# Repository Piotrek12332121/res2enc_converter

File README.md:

# res2enc_converter
It's a low-cost resolver2encoder converter to convert signals in motors found in old industrial robots

It uses AD2S1210 chip to generate excitation signals for resolver, measure analog signals, convert them and generate encoder-like signals that can be used with modern servo drives. Board can be powered by 24 or 12 V and has opto-isolated output.

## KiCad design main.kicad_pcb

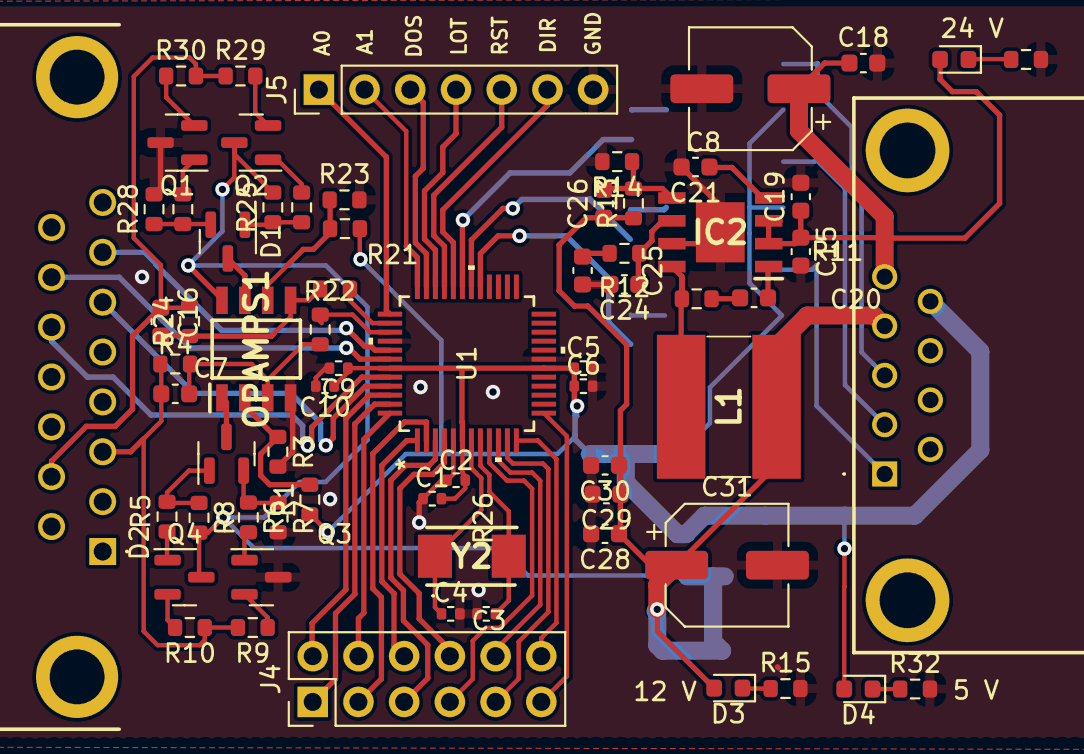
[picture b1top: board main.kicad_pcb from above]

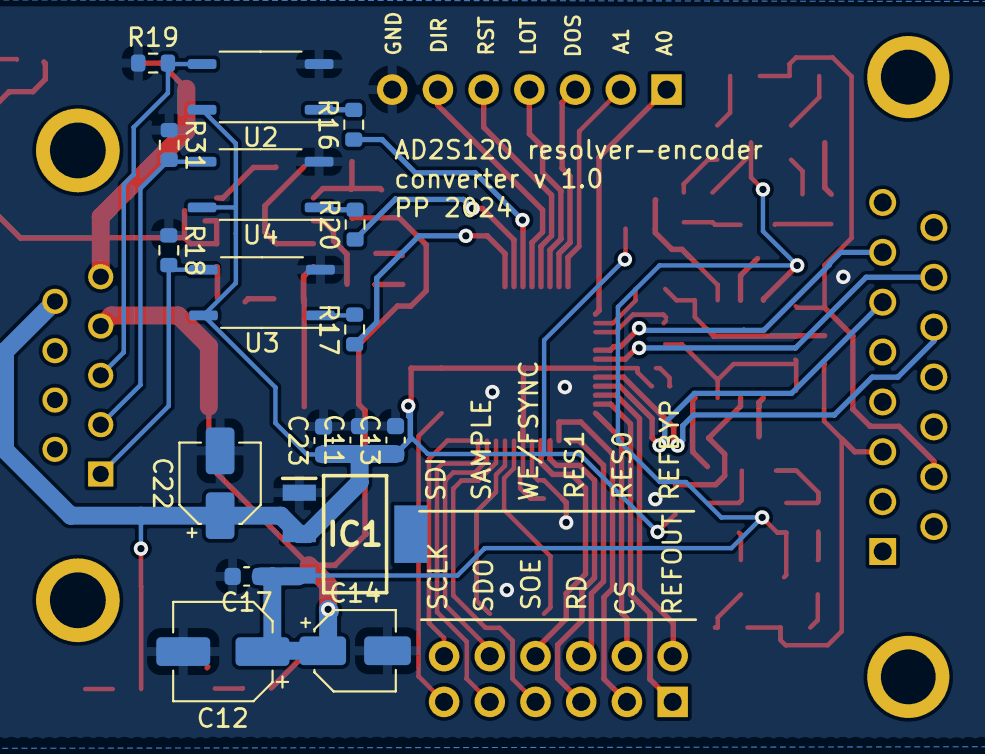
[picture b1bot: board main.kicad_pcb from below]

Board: 2 copper layers, 85 parts (17 on the bottom side), 69 nets.

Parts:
C1, C6, C10: 4.7 uF; R_0402_1005Metric
C2, C5, C9: 10 nF; R_0402_1005Metric
C3, C4: 18 pF; R_0402_1005Metric
C7, C16: C; C_0603_1608Metric
C8: 100u; CP_Elec_6.3x7.7
C11, C13, C15, C18, C19, C28, C29, C30: 10u; C_0603_1608Metric
C12: 50 uF; CP_Elec_5x5.4
C14: 10 uF; CP_Elec_4x5.4
C17, C23: 100 nF; C_0603_1608Metric
C20: 100n; C_0603_1608Metric
C21: 10n; C_0603_1608Metric
C22: 22 uF; CP_Elec_4x5.4
C24: 15p; C_0603_1608Metric
C25: 2n7; C_0603_1608Metric
C26: 100p; C_0603_1608Metric
C31: 100u; CP_Elec_6.3x5.4
D1, D2: BAV99; SOT-23
D3, D4, D5: LED; LED_0603_1608Metric
IC1: AZ1117CH-5.0TRG1; SOT230P700X170-4N
IC2: AP64501SP-13; SOIC127P600X163-9N
J2: DS1037-01-15FNAKSI74; DS10370115FNAKSI74
J3: LD09P13A4GX00LF
J4: Conn_02x06_Counter_Clockwise; PinHeader_2x06_P2.54mm_Vertical
J5: Conn_01x07_Pin; PinHeader_1x07_P2.54mm_Vertical
L1: 10u; SDR0805100ML
OPAMPS1: TL082CD; SOIC127P600X175-8N
Q1, Q3: BC807; SOT-23
Q2, Q4: BC817; SOT-23
R1, R2, R3, R4, R5, R6, R7, R8, R9, R10, R21, R22, R23, R24, R25, R26, R27, R28, R29, R30: R; R_0603_1608Metric
R11: 10R; R_0603_1608Metric
R12: 37k; R_0603_1608Metric
R13: 309k; R_0603_1608Metric
R14: 22k; R_0603_1608Metric
R15, R32: 2k7; R_0603_1608Metric
R16, R17, R18, R19, R20, R31: 1k; R_0603_1608Metric
R33: 20k; R_0603_1608Metric
U1: AD2S1210WDSTZ; AD2S1210WDSTZ_ADI
U2, U3, U4: TLP185; SOIC-4_4.55x3.7mm_P2.54mm
Y2: ABM3-8.192MHZ-B4Y-T; ABM3

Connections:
12_V: C12.1, C14.1, C17.1, C26.1, C28.1, C29.1, C30.1, C31.1, D3.2 (A), IC1.3 (INPUT), J3.4, L1.2, OPAMPS1.8 (VCC+), Q2.3 (C), Q4.3 (C), R8.2, R13.1, R25.2
/EXC: R22.1, U1.38 (EXC)
/optoisolation/A: R17.1, U1.29 (A)
/optoisolation/B: R20.1, U1.30 (B)
/optoisolation/NM: R16.1, U1.31 (NM)
/~EXC: R2.1, U1.39 (EXC)
A0: J5.1, U1.37 (A0)
A1: J5.2, U1.36 (A1)
CS: J4.3, U1.2 (CS)
DIR: J5.6, U1.32 (DIR)
DOS: J5.3, U1.35 (DOS)
ENCODER_EMULATE_A: J3.1, R18.2, U3.4
ENCODER_EMULATE_B: J3.2, R31.2, U4.4
ENCODER_EMULATE_NM: J3.3, R19.2, U2.4
EXTERNAL_5V: C1.2, C2.2, C5.1, C6.1, C9.1, C10.1, C11.1, C13.1, C22.1, C23.1, D4.2 (A), IC1.2 (OUTPUT), J3.9, R1.1, R21.1, U1.6 (DVDD), U1.18 (VDRIVE), U1.43 (AVDD), U2.6, U3.6, U4.6
EXTERNAL_24V: C8.1, C15.1, C18.1, C19.1, D5.2 (A), IC2.2 (VIN), IC2.3 (EN), J3.5
GND: C1.1, C2.1, C3.2, C4.2, C5.2, C6.2, C8.2, C9.2, C10.2, C11.2, C12.2, C13.2, C14.2, C15.2, C17.2, C18.2, C19.2, C21.2, C22.2, C23.2, C24.2, C25.2, C28.2, C29.2, C30.2, C31.2, IC1.1 (ADJ/GND), IC2.7 (GND), IC2.9 (EP), J5.7, OPAMPS1.4 (VCC-), Q1.3 (C), Q3.3 (C), R3.2, R7.2, R14.2, R15.2, R18.1, R19.1, R23.2, R28.2, R31.1, R32.2, R33.2, U1.5 (DGND), U1.19 (DGND), U1.40 (AGND), U2.3, U3.3, U4.3
LOT: J5.4, U1.34 (LOT)
unnamed: C7.1, OPAMPS1.3 (+), R2.2, R4.1
unnamed: C16.1, OPAMPS1.5 (+), R22.2, R24.1
unnamed: C20.1, R11.1
unnamed: C25.1, R12.2
unnamed: D1.2 (A), R27.1, R28.1
unnamed: D1.1 (K), R25.1, R26.2
unnamed: D2.2 (A), R6.1, R7.1
unnamed: D2.1 (K), R5.2, R8.1
unnamed: D3.1 (K), R15.1
unnamed: D4.1 (K), R32.1
unnamed: D5.1 (K), R33.1
unnamed: C20.2, IC2.1 (BST)
unnamed: C24.1, IC2.6 (COMP), R12.1
unnamed: C26.2, IC2.5 (FB), R13.2, R14.1
unnamed: C21.1, IC2.4 (SS)
unnamed: IC2.8 (SW), L1.1, R11.2
unnamed: OPAMPS1.2 (-), R1.2, R3.1
unnamed: OPAMPS1.6 (-), R21.2, R23.1
unnamed: D1.3 (K), OPAMPS1.7 (OUTPUT_2)
unnamed: D2.3 (K), OPAMPS1.1 (output_1)
unnamed: Q1.1 (B), R27.2
unnamed: Q1.2 (E), R30.1
unnamed: Q2.1 (B), R26.1
unnamed: Q2.2 (E), R29.2
unnamed: Q3.1 (B), R6.2
unnamed: Q3.2 (E), R9.1
unnamed: Q4.1 (B), R5.1
unnamed: Q4.2 (E), R10.2
unnamed: R16.2, U2.1
unnamed: R17.2, U3.1
unnamed: R20.2, U4.1
unnamed: C4.1, U1.7 (CLKIN), Y2.1
unnamed: C3.1, U1.8 (XTALOUT), Y2.2
R1: C7.2, J2.3, R4.2, R9.2, R10.1
R2: C16.2, J2.10, R24.2, R29.1, R30.2
RD: J4.5, U1.3 (RD)
REFBYP: J4.2, U1.46 (REFBYP)
REFOUT: J4.1, U1.47 (REFOUT)
RES0: J4.4, U1.48 (RES0)
RES1: J4.6, U1.1 (RES1)
RESET: J5.5, U1.33 (RESET)
S1: J2.7, U1.41 (SIN)
S2: J2.6, U1.45 (COS)
S3: J2.14, U1.42 (SINLO)
S4: J2.13, U1.44 (COSLO)
SAMPLE: J4.10, U1.10 (SAMPLE)
SCLK: J4.11, U1.13 (DB13/SCLK)
SDI: J4.12, U1.12 (DB14/SDI)
SDO: J4.9, U1.11 (DB15/SDO)
SOE: J4.7, U1.9 (SOE)
WR/FSYNC: J4.8, U1.4 (WR/FSYNC)

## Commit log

2024-10-17 Initial commit with ver 1.0 of board, prototype not tested
2024-10-17 Update README.md
    added short description
